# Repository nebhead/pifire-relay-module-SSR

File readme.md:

# PiFire Solid State Relay (SSR) Module PCB (v1.0.2) KiCad Files

## What is this? 

This PCB is designed to support mechanical relays for controlling incoming Power(L) to the Igniter, Auger, and AC Fan.  This board uses compact solid state relays that are able to handle high power. This is an alternative to using an off the shelf relay module which simplifies the wiring and even allows you to use the OEM harness.  

The design intent for this board was to make a DIY accessible PCB that can be more easily put together by the maker/enthusiast of almost any skill level.  Full size components are used in most cases and most (if not all) parts should be readily available to order online.  See the [Interactive BOM](#interactive-bom) for more details about the parts used and links to order.

### What is PiFire? 

PiFire is a SBC based Pellet Smoker Controller.  More details can be found [here](https://nebhead.github.io/PiFire) or [at the GitHub repo](https://github.com/nebhead/pifire). 

## What's in this Repository?

### KiCad Project Files 
In this repository you will find the latest KiCad design files for the  PCB.  Simply load the project file (.kicad_pro) into the KiCad software and you should be able to edit as needed.  Or if you just want to get this board made, jump to the production section below.

### Interactive BOM

There is an interactive BOM located in the [/bom](bom/) folder which details the parts and provides some pin information as well.  Use this to gather the components you may need to build this board out and refer back to it for placement help.    

[BOM + Pin Info](https://nebhead.github.io/pifire-relay-module-SSR)

_This is a standalone HTML file that was autogenerated by the excellent plugin for KiCad. See the plugin here: [https://github.com/openscopeproject/InteractiveHtmlBom](https://github.com/openscopeproject/InteractiveHtmlBom)_

### PDF of the Schematic

Preview the schematic in PDF format here: [Schematic](schematic.pdf)

### JLCPCB Production Files

If you wish to get these PCBs made by JLCPCB, the production files are provided in the `/production` folder.  For convenience, the file `production.zip` can simply be uploaded to JLCPCB to make it super easy to order boards.

Drop the zip file onto the order page, wait for it to upload then simply continue to order the board.  Optionally, select different board color, PCB quantity, surface finish, etc.  Most of the default settings should be sufficient. 

### Links to the PCBs in this family of PiFire Boards

This PCB is part of a family of PCBs that can be used together to create  a full PiFire system.  Generally speaking you need the Main Module/Board, a Relay Control Board and a Probe Device board to have a basic PiFire system.  

**Main Module/Board** (required)
* [Main Board v4.0.x](https://github.com/nebhead/pifire-main-module-nopwr)

**Relay/Fan Control Boards** (choose one)
* [Mechanical Relay Module](https://github.com/nebhead/pifire-relay-module)
* [Solid State Relay Module](https://github.com/nebhead/pifire-relay-module-ssr)
* [Solid State Relay + PWM Fan Module](https://github.com/nebhead/pifire-relay-pwm-module-ssr) - Original Design
* [Solid State Relay + PWM Fan Module Alternate](https://github.com/nebhead/pifire-relay-pwm-module-ssr-alt) - Updated Design (Designed with help from @labmonkeyrat on Discord)

**Probe Device Board** (optional)
* [ADS Board](https://github.com/nebhead/pifire-ads-board) 

### 3D Printable Enclosures/Boxes 

With all of the 3D Prints for PiFire, a higher temperature filament such as PETG should be used.  PLA generally won't stand up to the temperatures that the components may be exposed to outdoors and near a hot smoker.  

#### Enclosure

Included here is an initial revision of the enclosure for this PCB.  The current models should be considered still in development and may have alignment challenges, etc. 

Except for the mounting wings, the majority of bolts to be used with this enclosure are M3. 

* STL: [Base](/printables/PiFire-v4-Relay-Base.stl)
* STL: [Lid](/printables/PiFire-v4-Relay-Lid.stl)
* OnShape: [Enclosure Original Models](https://cad.onshape.com/documents/03559f76f7adf190bf6f1259/w/7529cb0e4cd69db1a6a15202/e/07d5f9d46dc8f2b9e7dd655f?renderMode=0&uiState=66e11de950d7684b88999a0f)

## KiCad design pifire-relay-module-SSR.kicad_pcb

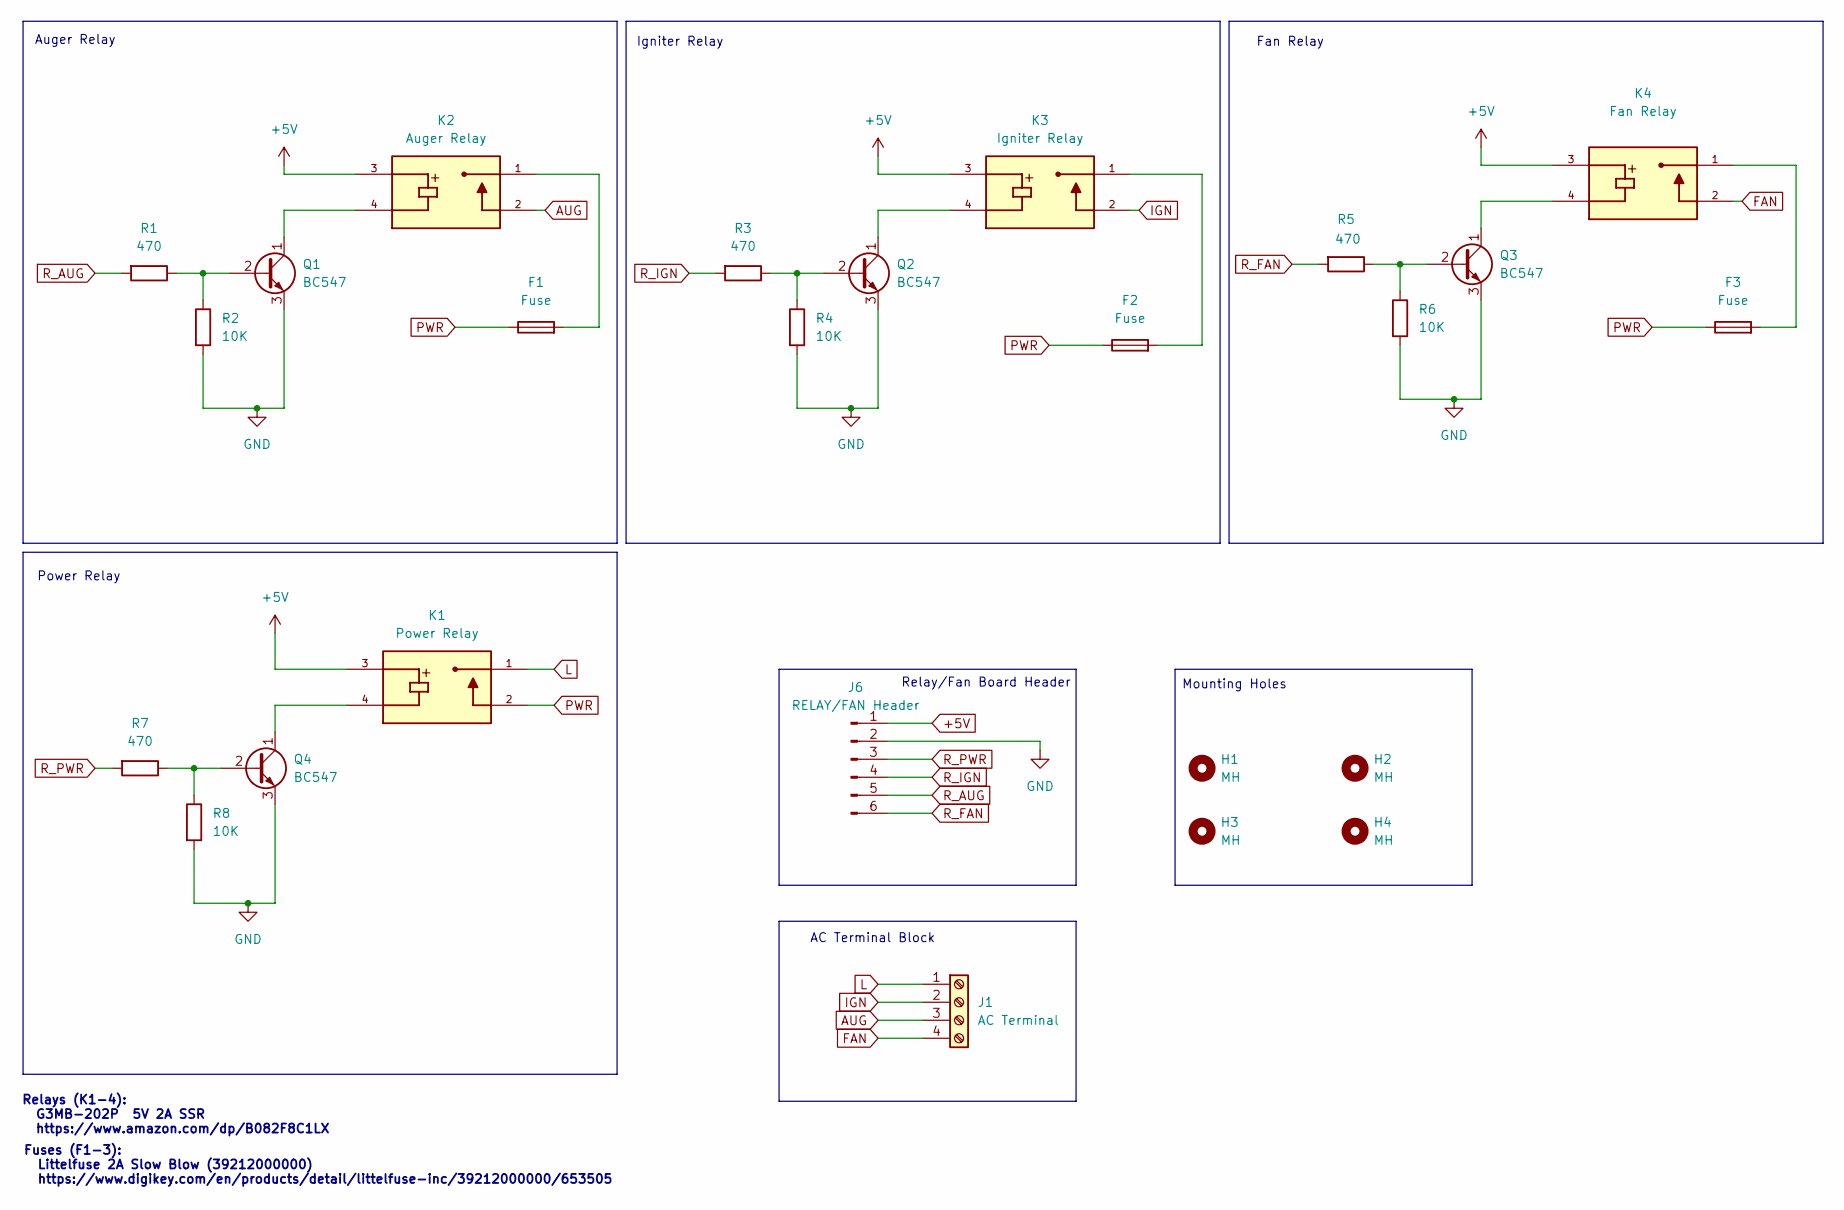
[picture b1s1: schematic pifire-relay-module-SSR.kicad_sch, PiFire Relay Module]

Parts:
F1, F2, F3: Fuse; Fuse_Littelfuse_395Series
H1, H2, H3, H4: MH; MountingHole_3.2mm_M3
J1: AC Terminal; TerminalBlock_bornier-4_P5.08mm
J6: RELAY/FAN Header; JST_XH_B6B-XH-A_1x06_P2.50mm_Vertical
K1: Power Relay; RELAY_G3MB-202PDC5; PARTREV J091-E1-1A
K2: Auger Relay; RELAY_G3MB-202PDC5; PARTREV J091-E1-1A
K3: Igniter Relay; RELAY_G3MB-202PDC5; PARTREV J091-E1-1A
K4: Fan Relay; RELAY_G3MB-202PDC5; PARTREV J091-E1-1A
Q1, Q2, Q3, Q4: BC547; TO-92L_Inline
R1, R3, R5, R7: 470; R_Axial_DIN0207_L6.3mm_D2.5mm_P7.62mm_Horizontal
R2, R4, R6, R8: 10K; R_Axial_DIN0207_L6.3mm_D2.5mm_P7.62mm_Horizontal

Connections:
+5V: J6.1, K1.3, K2.3, K3.3, K4.3
AUG: J1.3, K2.2
FAN: J1.4, K4.2
GND: J6.2, Q1.3 (E), Q2.3 (E), Q3.3 (E), Q4.3 (E), R2.2, R4.2, R6.2, R8.2
IGN: J1.2, K3.2
L: J1.1, K1.1
unnamed: F1.2, K2.1
unnamed: F2.2, K3.1
unnamed: F3.2, K4.1
unnamed: Q1.2 (B), R1.1, R2.1
unnamed: K2.4, Q1.1 (C)
unnamed: Q2.2 (B), R3.1, R4.1
unnamed: K3.4, Q2.1 (C)
unnamed: Q3.2 (B), R5.1, R6.1
unnamed: K4.4, Q3.1 (C)
unnamed: Q4.2 (B), R7.1, R8.1
unnamed: K1.4, Q4.1 (C)
PWR: F1.1, F2.1, F3.1, K1.2
R_AUG: J6.5, R1.2
R_FAN: J6.6, R5.2
R_IGN: J6.4, R3.2
R_PWR: J6.3, R7.2

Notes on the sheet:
Fan Relay
Power Relay
Fuses (F1-3): Littelfuse 2A Slow Blow (39212000000) https://www.digikey.com/en/products/detail/littelfuse-inc/39212000000/653505
AC Terminal Block
Auger Relay
Relay/Fan Board Header
Relays (K1-4): G3MB-202P 5V 2A SSR https://www.amazon.com/dp/B082F8C1LX
Mounting Holes
Igniter Relay

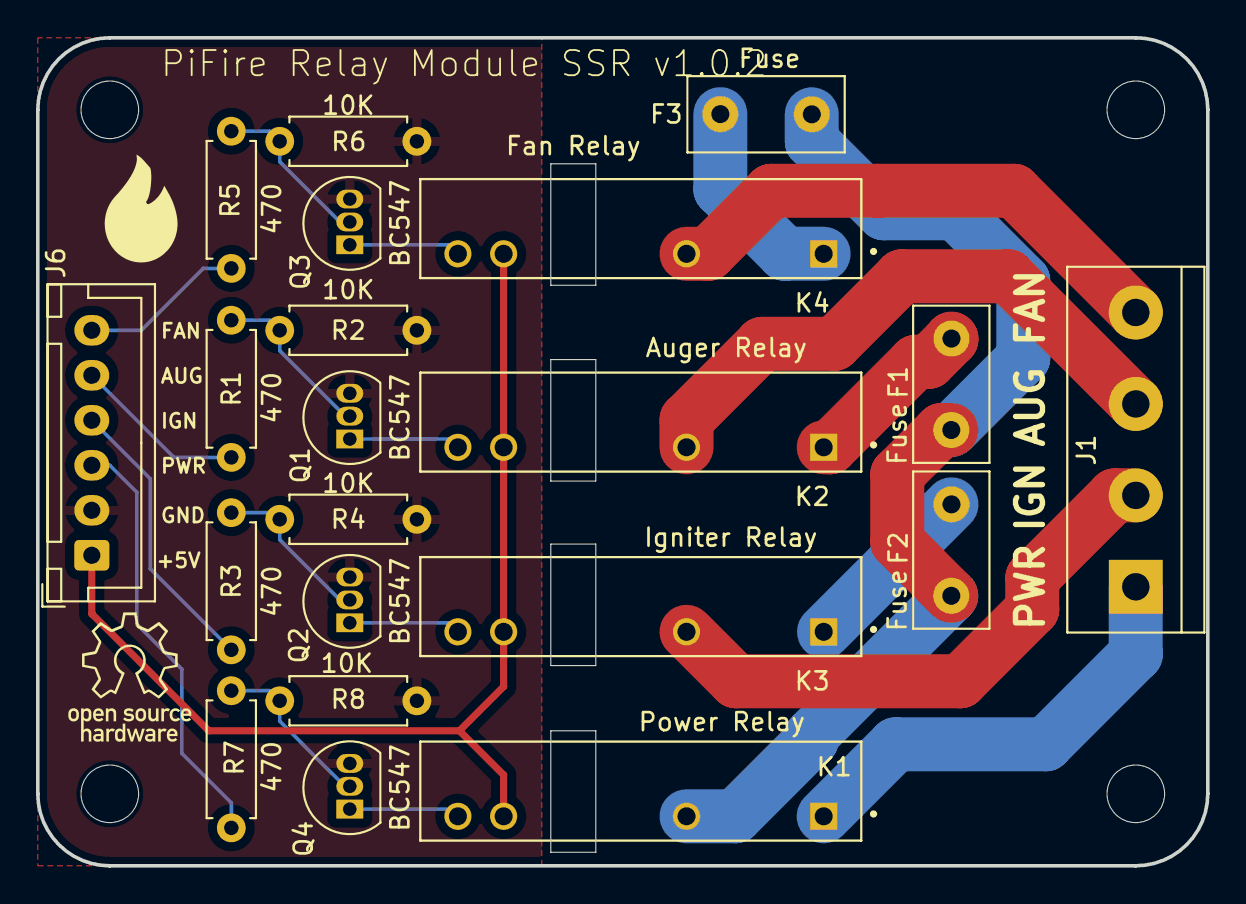
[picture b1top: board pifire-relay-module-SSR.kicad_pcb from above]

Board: 2 copper layers, 65.0 x 46.0 mm, 25 parts (0 on the bottom side), 22 nets.

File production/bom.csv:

Designator,Footprint,Quantity,Value,LCSC Part #
"F1, F2, F3",Fuse_Littelfuse_395Series,3,Fuse,
"H1, H2, H3, H4",MountingHole_3.2mm_M3,4,MH,
J1,TerminalBlock_bornier-4_P5.08mm,1,AC Terminal,
J6,JST_XH_B6B-XH-A_1x06_P2.50mm_Vertical,1,RELAY/FAN Header,
K1,RELAY_G3MB-202PDC5,1,Power Relay,
K2,RELAY_G3MB-202PDC5,1,Auger Relay,
K3,RELAY_G3MB-202PDC5,1,Igniter Relay,
K4,RELAY_G3MB-202PDC5,1,Fan Relay,
"Q1, Q2, Q3, Q4",TO-92L_Inline,4,BC547,
"R1, R3, R5, R7",R_Axial_DIN0207_L6.3mm_D2.5mm_P7.62mm_Horizontal,4,470,
"R2, R4, R6, R8",R_Axial_DIN0207_L6.3mm_D2.5mm_P7.62mm_Horizontal,4,10K,

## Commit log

2024-05-10 Added license.txt
2024-05-10 Fix link to bom html
2024-05-10 Fix link to bom
2024-05-10 Third time is the charm...
2024-09-07 Update readme.md
    Update links for PWM boards.
2024-09-11 Auto stash before merge of "main" and "origin/main"
2025-12-24 Updated to V1.0.2
    This version is a minor update to change 4.7k Ohm resistor values to 470 Ohms. Some users had pointed out that the 4.7k Ohm resistors may be too large and may not allow the transistors to properly tu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
2025-12-27 Updated v1.0.2 December on backside
